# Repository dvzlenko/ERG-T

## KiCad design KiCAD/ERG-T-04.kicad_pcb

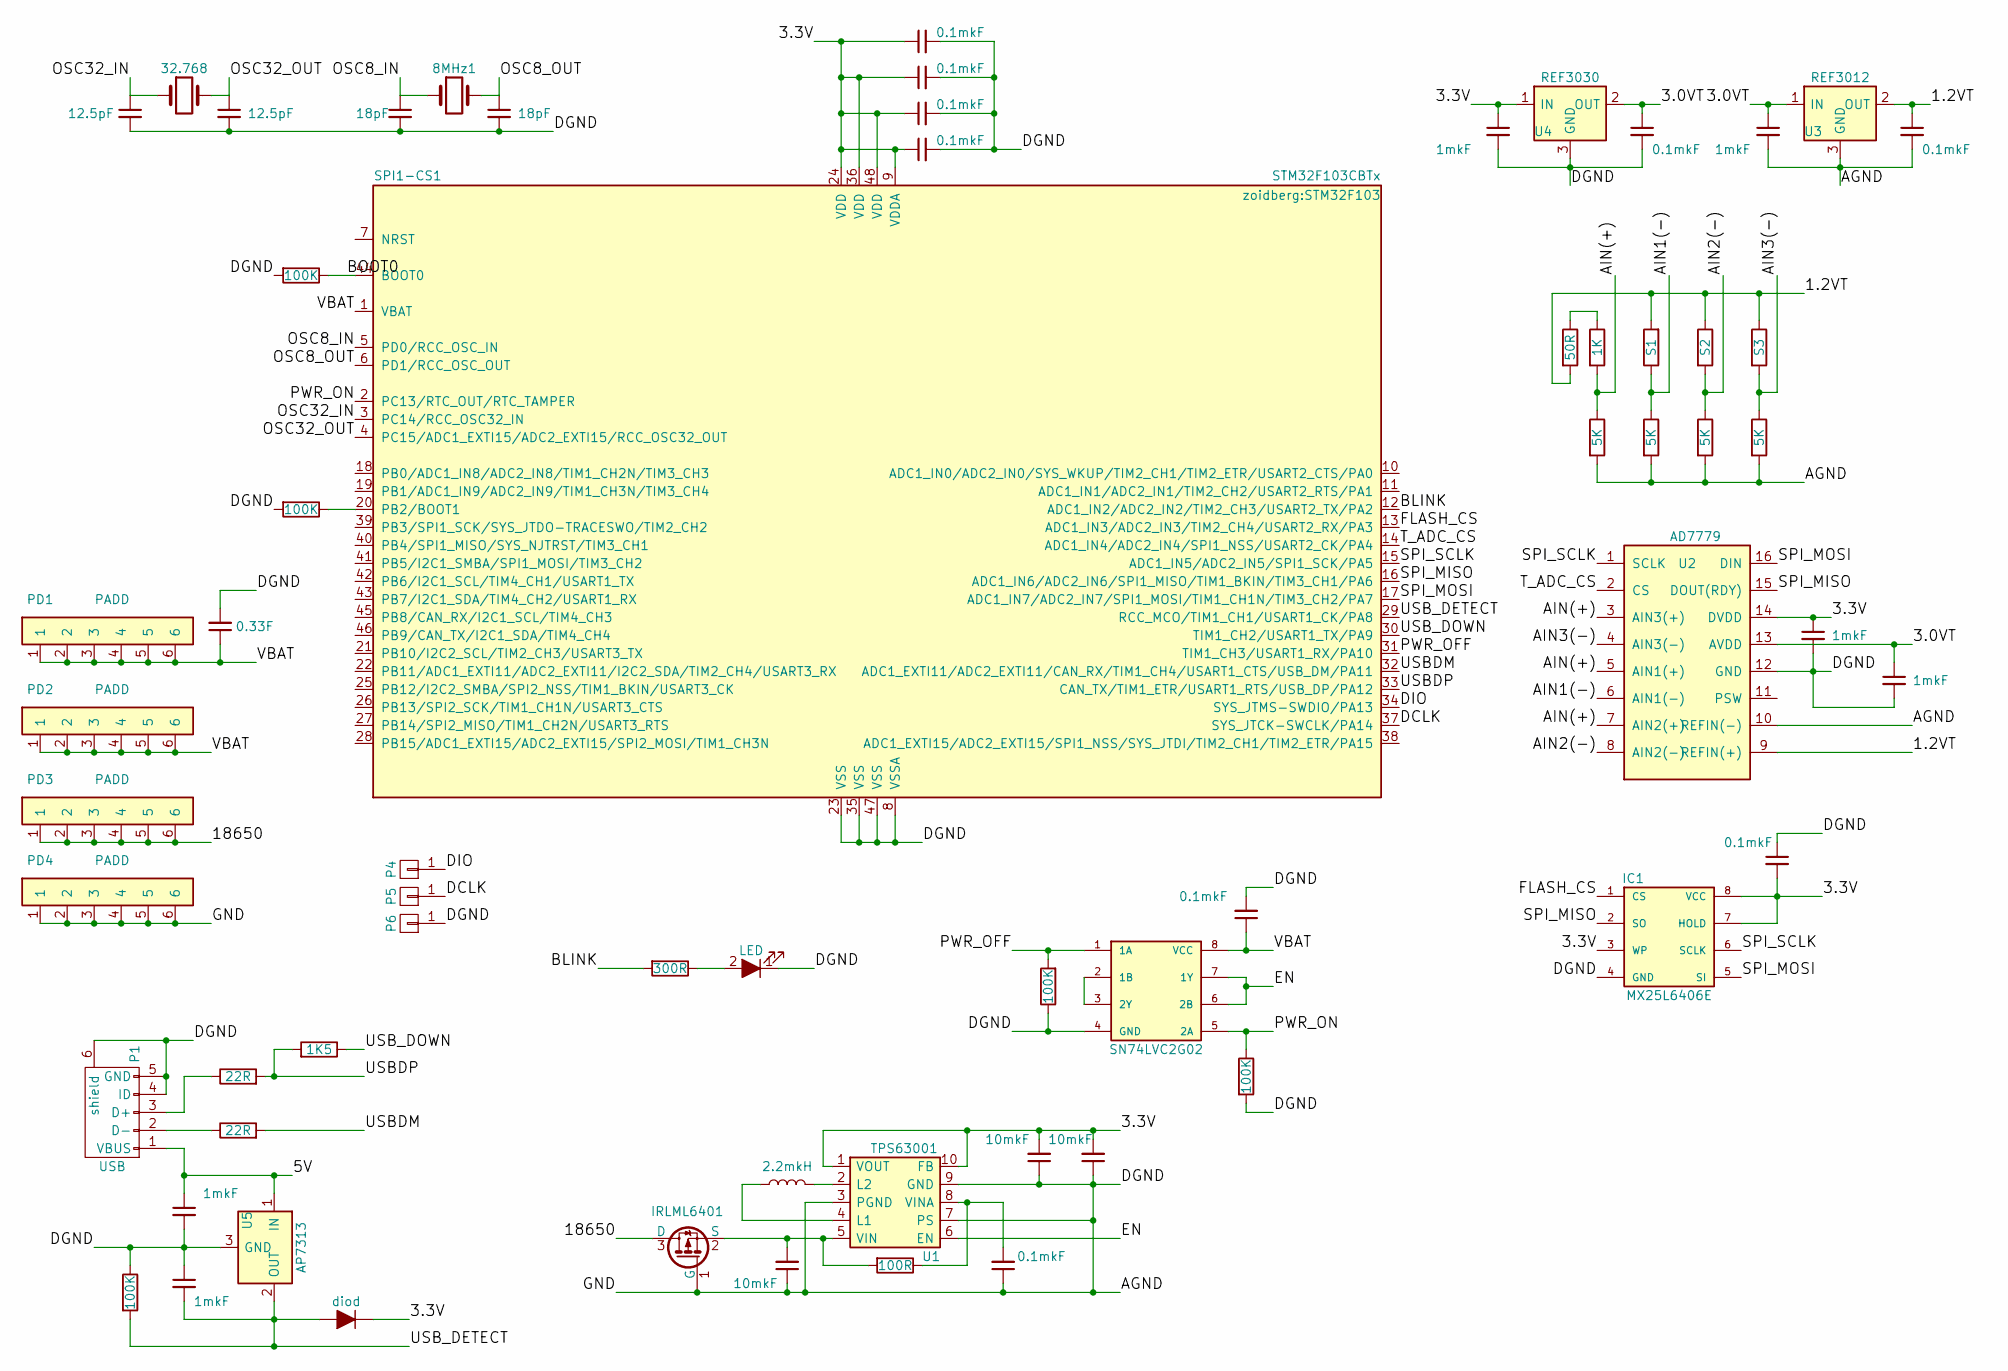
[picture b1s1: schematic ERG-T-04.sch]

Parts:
8MHz1: 8MHz; Crystal_HC49-U_Vertical
32.768: 32kHz; Crystal_Round_d3.0mm_Vertical
C1, C3: 12.5pF; C_0805
C2, C4: 18pF; C_0805
C5, C8, C22: 10mkF; C_0805
C6, C7, C12, C14, C16, C18, C19, C20, C23: 0.1mkF; C_0805
C9, C10, C11, C13, C15, C17: 1mkF; C_0805
C21: 0.33F; PAN-IONISTOR
D1: diod; D_SOD-123
D2: LED; LED_0805
IC1: MX25L6406E; MX25L64
IC2: SN74LVC2G02
L1: 2.2mkH; L_1812
P1: USB; USB_Micro-B
P4: DIO; UART-PIN
P5: DCLK; UART-PIN
P6: GND; UART-PIN
PD1, PD2, PD3, PD4: PADD; pad_4.0x1.0_holes
Q1: IRLML6401; SOT-23
R1, R2, R9, R19, R20: 100K; R_0805
R3: 1K5; R_0805
R4, R5: 22R; R_0805
R6: 300R; R_0805
R7: 100R; R_0805
R10: 1K; R_Axial_DIN0207_L6.3mm_D2.5mm_P10.16mm_Horizontal
R11, R13, R15, R17: 5K; R_Axial_DIN0207_L6.3mm_D2.5mm_P10.16mm_Horizontal
R12: S1; 700-BAA-B00-SMD
R14: S2; 700-BAA-B00-SMD
R16: S3; 700-BAA-B00-SMD
R18: 50R; R_Axial_DIN0207_L6.3mm_D2.5mm_P10.16mm_Horizontal
SPI1-CS1: STM32F103CBTx; STM32F103
U1: TPS63001
U2: AD7779; TSSOP-16_4.4x5mm_Pitch0.65mm
U3: REF3012; SOT-23
U4: REF3030; SOT-23
U5: AP7313

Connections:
/1.2VT: C18.1, R12.2, R14.1, R16.1, R18.2, U2.9 (REFIN(+)), U3.2 (OUT)
/3.0VT: C12.1, C13.1, C17.1, U2.13 (AVDD), U3.1 (IN), U4.2 (OUT)
/3.3V: C7.1, C8.2, C11.1, C14.2, C15.1, C16.1, C19.1, C20.1, C22.2, D1.1 (K), IC1.3 (WP), IC1.7 (HOLD), IC1.8 (VCC), SPI1-CS1.9 (VDDA), SPI1-CS1.24 (VDD), SPI1-CS1.36 (VDD), SPI1-CS1.48 (VDD), U1.1 (VOUT), U1.10 (FB), U2.14 (DVDD), U4.1 (IN)
/5V: C9.1, P1.1 (VBUS), U5.1 (IN)
/18650: PD3.1, PD3.2, PD3.3, PD3.4, PD3.5, PD3.6, Q1.3 (D)
/AGND: C1.2, C2.2, C3.2, C4.2, C5.1, C6.1, C7.2, C8.1, C9.2, C10.1, C11.2, C12.2, C13.2, C14.1, C15.2, C16.2, C17.2, C18.2, C19.2, C20.2, C21.2, C22.1, C23.2, D2.1 (K), IC1.4 (GND), IC2.4 (GND), P1.4 (ID), P1.5 (GND), P1.6 (shield), P6.1, PD4.1, PD4.2, PD4.3, PD4.4, PD4.5, PD4.6, Q1.1 (G), R1.2, R2.2, R9.1, R11.2, R13.2, R15.2, R17.2, R19.1, R20.2, SPI1-CS1.8 (VSSA), SPI1-CS1.23 (VSS), SPI1-CS1.35 (VSS), SPI1-CS1.47 (VSS), U1.3 (PGND), U1.7 (PS), U1.9 (GND), U2.10 (REFIN(-)), U2.12 (GND), U3.3 (GND), U4.3 (GND), U5.3 (GND)
/AIN1(-): R12.1, R13.1, U2.6 (AIN1(-))
/AIN2(-): R14.2, R15.1, U2.8 (AIN2(-))
/AIN3(-): R16.2, R17.1, U2.4 (AIN3(-))
/AIN(+): R10.2, R11.1, U2.3 (AIN3(+)), U2.5 (AIN1(+)), U2.7 (AIN2(+))
/BLINK: R6.2, SPI1-CS1.12 (ADC1_IN2/ADC2_IN2/TIM2_CH3/USART2_TX/PA2)
/BOOT0: R2.1, SPI1-CS1.44 (BOOT0)
/DCLK: P5.1, SPI1-CS1.37 (SYS_JTCK-SWCLK/PA14)
/DIO: P4.1, SPI1-CS1.34 (SYS_JTMS-SWDIO/PA13)
/EN: IC2.6 (2B), IC2.7 (1Y), U1.6 (EN)
/FLASH_CS: IC1.1 (CS), SPI1-CS1.13 (ADC1_IN3/ADC2_IN3/TIM2_CH4/USART2_RX/PA3)
/OSC8_IN: 8MHz1.1, C2.1, SPI1-CS1.5 (PD0/RCC_OSC_IN)
/OSC8_OUT: 8MHz1.2, C4.1, SPI1-CS1.6 (PD1/RCC_OSC_OUT)
/OSC32_IN: 32.768.1, C1.1, SPI1-CS1.3 (PC14/RCC_OSC32_IN)
/OSC32_OUT: 32.768.2, C3.1, SPI1-CS1.4 (PC15/ADC1_EXTI15/ADC2_EXTI15/RCC_OSC32_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)
/PWR_OFF: IC2.1 (1A), R19.2, SPI1-CS1.31 (TIM1_CH3/USART1_RX/PA10)
/PWR_ON: IC2.5 (2A), R20.1, SPI1-CS1.2 (PC13/RTC_OUT/RTC_TAMPER)
/SPI_MISO: IC1.2 (SO), SPI1-CS1.16 (ADC1_IN6/ADC2_IN6/SPI1_MISO/TIM1_BKIN/T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), U2.15 (DOUT(RDY))
/SPI_MOSI: IC1.5 (SI), SPI1-CS1.17 (ADC1_IN7/ADC2_IN7/SPI1_MOSI/TIM1_CH1N/T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), U2.16 (DIN)
/SPI_SCLK: IC1.6 (SCLK), SPI1-CS1.15 (ADC1_IN5/ADC2_IN5/SPI1_SCK/PA5), U2.1 (SCLK)
/T_ADC_CS: SPI1-CS1.14 (ADC1_IN4/ADC2_IN4/SPI1_NSS/USART2_CK/PA4), U2.2 (CS)
/USBDM: R4.2, SPI1-CS1.32 (ADC1_EXTI11/ADC2_EXTI11/CAN_RX/TIM1_CH4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)
/USBDP: R3.2, R5.2, SPI1-CS1.33 (CAN_TX/TIM1_ETR/USART1_RTS/USB_DP/PA12)
/USB_DETECT: C10.2, D1.2 (A), R9.2, SPI1-CS1.29 (RCC_MCO/TIM1_CH1/USART1_CK/PA8), U5.2 (OUT)
/USB_DOWN: R3.1, SPI1-CS1.30 (TIM1_CH2/USART1_TX/PA9)
/VBAT: C21.1, C23.1, IC2.8 (VCC), PD1.1, PD1.2, PD1.3, PD1.4, PD1.5, PD1.6, PD2.1, PD2.2, PD2.3, PD2.4, PD2.5, PD2.6, SPI1-CS1.1 (VBAT)
unnamed: C5.2, Q1.2 (S), R7.2, U1.5 (VIN)
unnamed: C6.2, R7.1, U1.8 (VINA)
unnamed: D2.2 (A), R6.1
unnamed: IC2.2 (1B), IC2.3 (2Y)
unnamed: L1.1, U1.4 (L1)
unnamed: L1.2, U1.2 (L2)
unnamed: P1.2 (D-), R4.1
unnamed: P1.3 (D+), R5.1
unnamed: R1.1, SPI1-CS1.20 (PB2/BOOT1)
unnamed: R10.1, R18.1

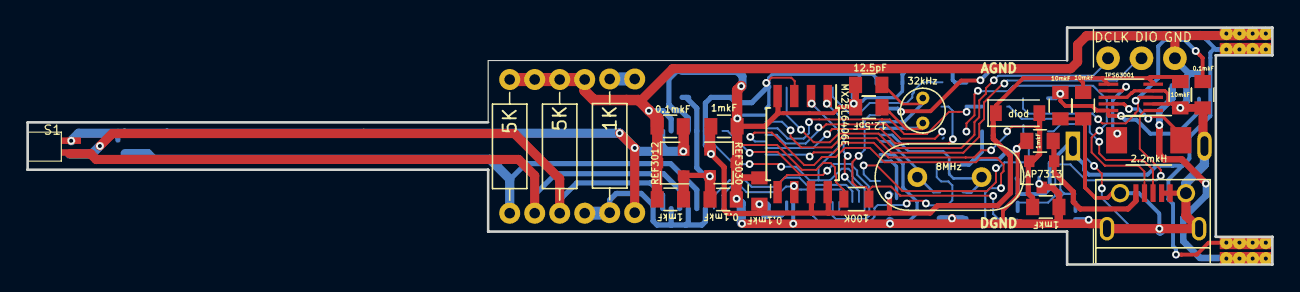
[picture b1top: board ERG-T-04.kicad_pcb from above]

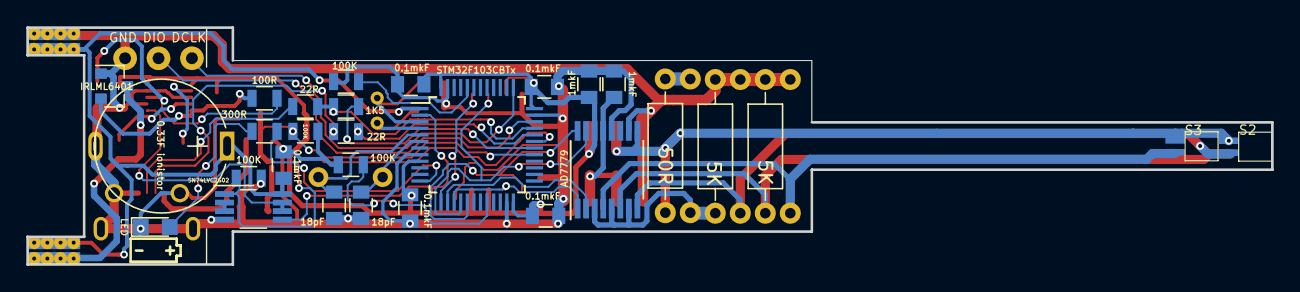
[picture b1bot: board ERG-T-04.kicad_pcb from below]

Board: 2 copper layers, 94.6 x 18.0 mm, 64 parts (32 on the bottom side), 41 nets.

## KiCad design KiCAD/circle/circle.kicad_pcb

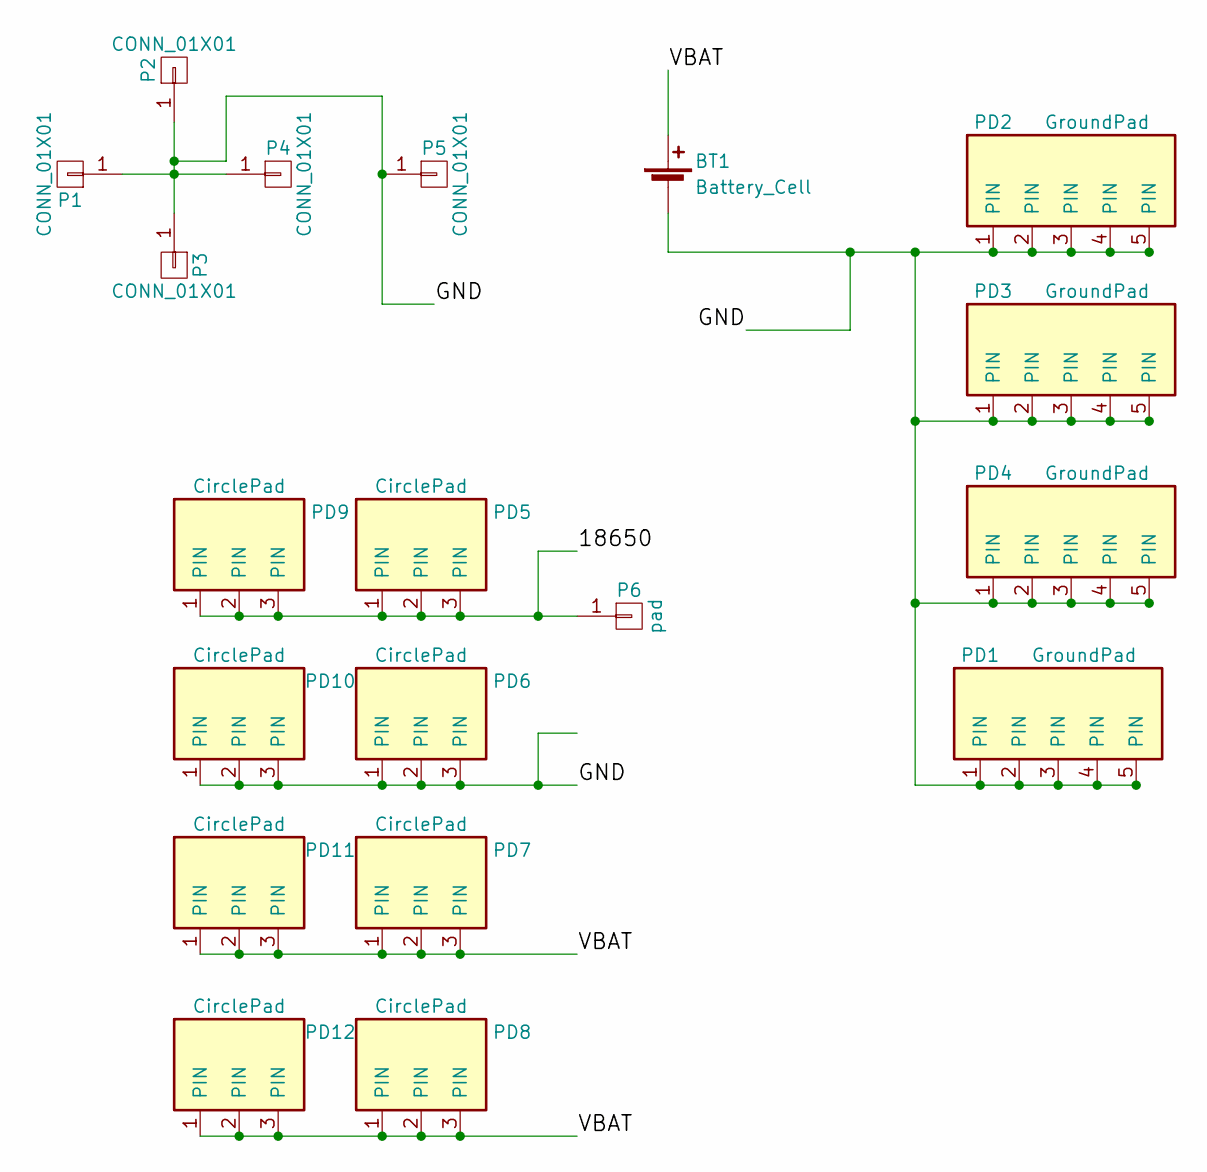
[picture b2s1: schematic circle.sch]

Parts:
BT1: Battery_Cell; Keystone_3001_1x12mm-CoinCell-VARIANT
P1, P2, P3, P4, P5: CONN_01X01; conn_1mm
P6: pad; conn_1mm
PD1, PD2, PD3, PD4: GroundPad; GroundPad-01
PD5, PD6, PD7, PD8, PD9, PD10, PD11, PD12: CirclePad; pad_1.5x1.0

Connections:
/18650: P6.1, P6.2, P6.3, P6.4, P6.5, PD5.1, PD5.2, PD5.3, PD9.1, PD9.2, PD9.3
/GND: BT1.2 (-), P1.1, P2.1, P3.1, P4.1, P5.1, PD1.1, PD1.2, PD1.3, PD1.4, PD1.5, PD2.1, PD2.2, PD2.3, PD2.4, PD2.5, PD3.1, PD3.2, PD3.3, PD3.4, PD3.5, PD4.1, PD4.2, PD4.3, PD4.4, PD4.5, PD6.1, PD6.2, PD6.3, PD10.1, PD10.2, PD10.3
/VBAT: BT1.1 (+), PD7.1, PD7.2, PD7.3, PD8.1, PD8.2, PD8.3, PD11.1, PD11.2, PD11.3, PD12.1, PD12.2, PD12.3

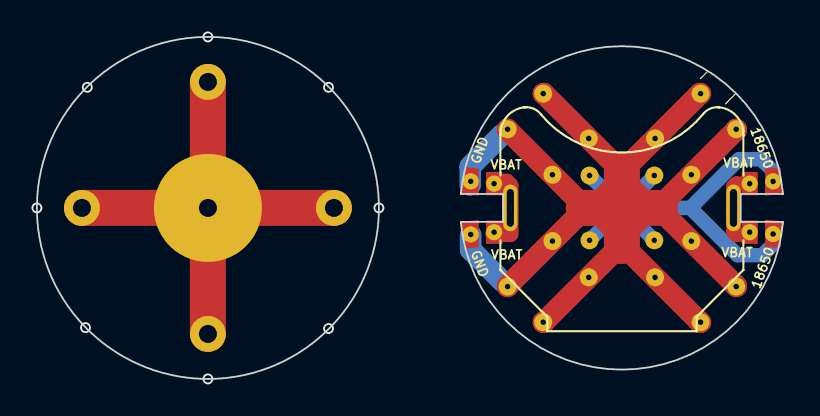
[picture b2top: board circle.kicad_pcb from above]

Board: 2 copper layers, 41.5 x 19.0 mm, 19 parts (1 on the bottom side), 3 nets.

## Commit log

2020-01-18 This is the initial commit. The snapshot represents the full structure of the ERG-T-03 device.
2020-01-20 Some garbage was removed from the code
2020-01-20 The "ZERO LENGTH PACKAGE" bug was fixed for N * 64bytes USB transactions
2020-01-20 Some garbage was removed
2020-01-21 Some roughnesses were fixed in VCP driver code
2020-09-18 Full ERG-TP maintainance + plotting stuff
2020-09-18 Date&Time bug on more than second timesteps was fixed
2020-09-18 some endpoint comments, not more
